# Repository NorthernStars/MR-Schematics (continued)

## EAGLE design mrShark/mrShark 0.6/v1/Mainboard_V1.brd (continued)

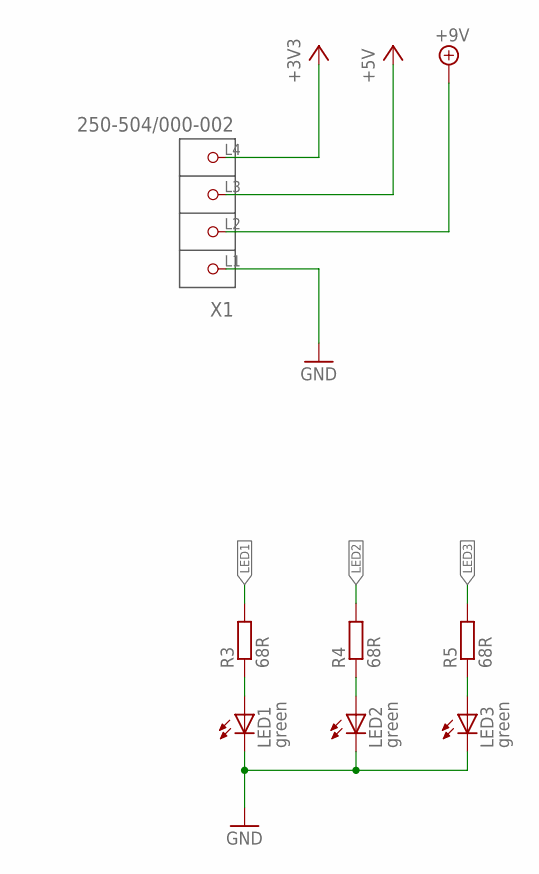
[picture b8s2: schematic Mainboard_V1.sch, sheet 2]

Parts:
LED1, LED2, LED3: green; CHIP-LED0805
R3, R4, R5: 68R; R0805W
X1: 250-504/000-002; P-250-504

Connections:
+3V3: X1.L4 (P4); also elsewhere on the board
+5V: X1.L3 (P3); also elsewhere on the board
+9V: X1.L2 (P2); also elsewhere on the board
GND: LED1.C, LED2.C, LED3.C, X1.L1 (P1); also elsewhere on the board
LED1: R3.2; also elsewhere on the board
LED2: R4.2; also elsewhere on the board
LED3: R5.2; also elsewhere on the board
unnamed: LED1.A, R3.1
unnamed: LED2.A, R4.1
unnamed: LED3.A, R5.1

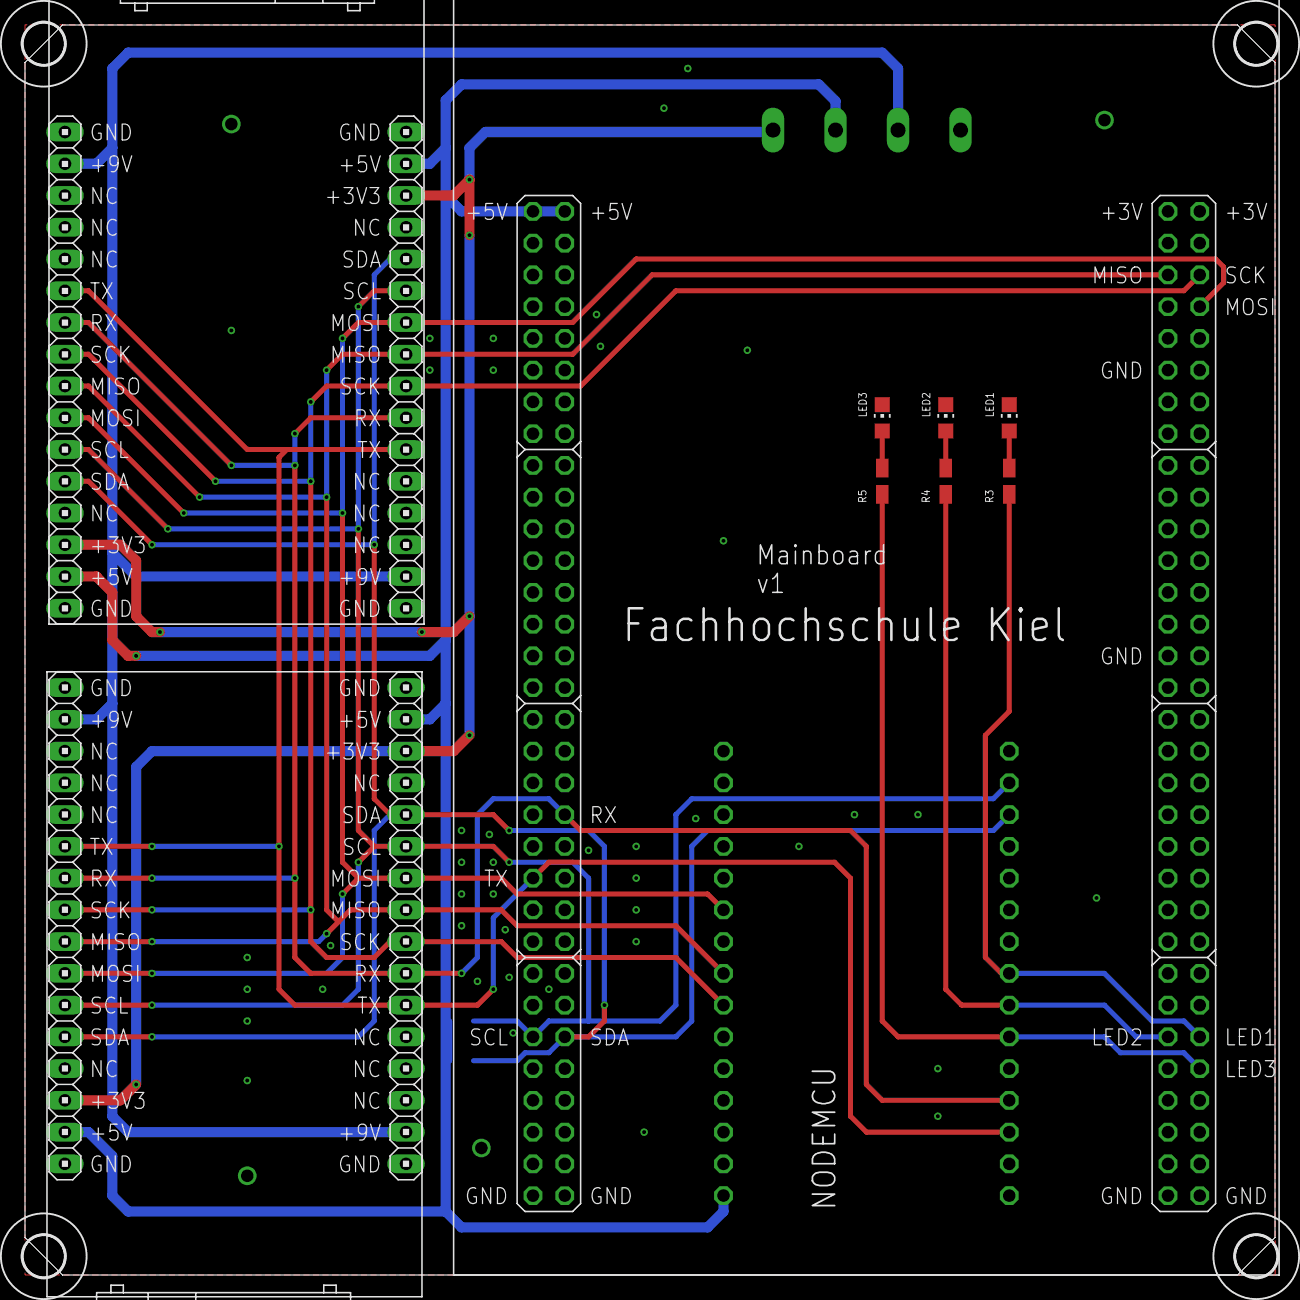
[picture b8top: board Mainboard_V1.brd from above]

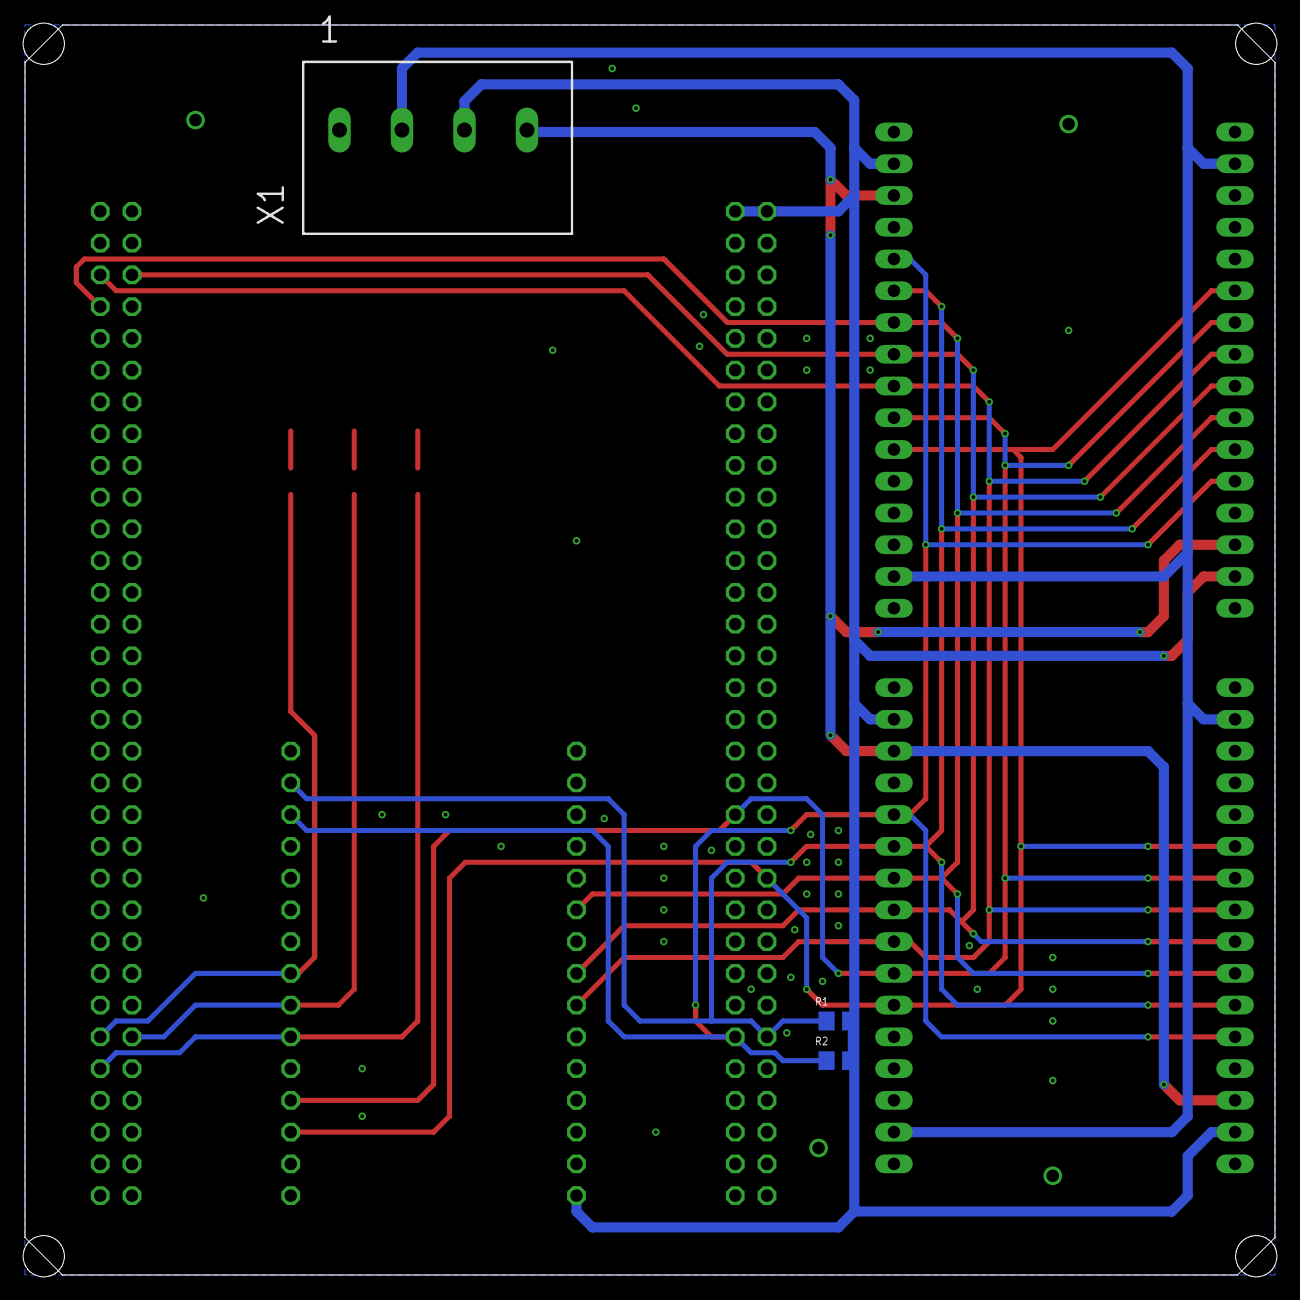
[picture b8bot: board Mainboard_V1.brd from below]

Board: 2 copper layers, 100.0 x 100.0 mm, 17 parts (3 on the bottom side), 17 nets.

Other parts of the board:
U$4, U$5, U$6, U$7: 3,3

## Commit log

2014-11-25 Restructured mrShark subdirectory.
2014-11-25 Updated LiPo-Charger MultiBoard schematic and board.
2014-11-26 Added Bot dimension to LiPo-Charger MultiBoard layout.
2014-11-26 Renamed Mulitboard charger board. Added MultiBoard Supply board.
2014-11-26 Updated schematics and board. Added LibreOffice calculation for part lists.
2014-11-26 Updated information for LiPo-Charger MulitBoard
2014-11-26 Fixed errors in LiPo-Charger-Station
2014-11-26 Updated IR-Splitter
2014-11-26 Added IR-Splitter README
2014-11-26 Changed size of IR_Transmitter to fit dirtypcbs.com 50x50mm size.
2014-11-26 Added a jumper to switch between USB power and extranl power for IR-Transmitter. Updated README.md
2014-11-30 Updated mrShark board layout to avoid electrict short circuits while charging with wrong board orientantion.
2014-11-30 Added mrShark board image
2015-01-06 Fixed IR-Transmitter board
2015-01-06 Updated LiPo-Charger Multiboard layout and parts calculation
2015-01-06 Updated mrShark v. 1.1 layout and schematic
2015-01-06 Updated mrShark v1.2 layout
2015-01-06 Updated mrShark Debugger layout
2015-01-16 Updated IR Splitter schematics and layout to avoid damage of IR leds
2015-01-22 Updated IR-Splitter to Version 1.0.0
2015-01-22 Added optional resistors R2 & R3 to schematics and layout.
2015-04-27 Updated mr Shark Layout and added LED-Marker
2015-05-06 Updated LED-marker to version 0.0.1
2015-05-06 Updated LED-marker
2015-05-06 Added switchable position lights
2015-05-06 Rename README to README.md
2015-05-27 Updated revision number in board layout.
2015-08-04 Updated mrShark 1.2 & 1.3 Updated mrShark Adapter Updated mrShark LED-Marker to version 0.0.3
2016-06-01 Updated LED Marker to version 1.0 Fixed a bug with wrong placed led and updated connection header layout.
2016-06-01 Updated mrShark to Version 1.4 Updated connector layout and fixed some corresponding layout errors.
2016-06-01 Updated to version 0.0.1 Updated connector layout
2016-06-01 Updated to new connector layout.
2016-06-01 Updated layouts and added parts lists
2016-07-12 Fixed error in board layout
2016-12-20 Added second version of mrShark Adapter that should be solderable by hand.
2017-01-30 Updated Board layouts an schematics
2017-01-30 Updated adapter to hirose mini usb connector
2017-02-16 Fixed layout errors. Layout is now tested.
2018-05-22 Updated README of LED Marker and Lists
2018-05-22 Updated layout and added gerber files.
2018-05-22 Fixed wrong files
